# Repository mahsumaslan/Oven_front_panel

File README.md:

# Oven_front_panel
It is a front panel pcb and test program.

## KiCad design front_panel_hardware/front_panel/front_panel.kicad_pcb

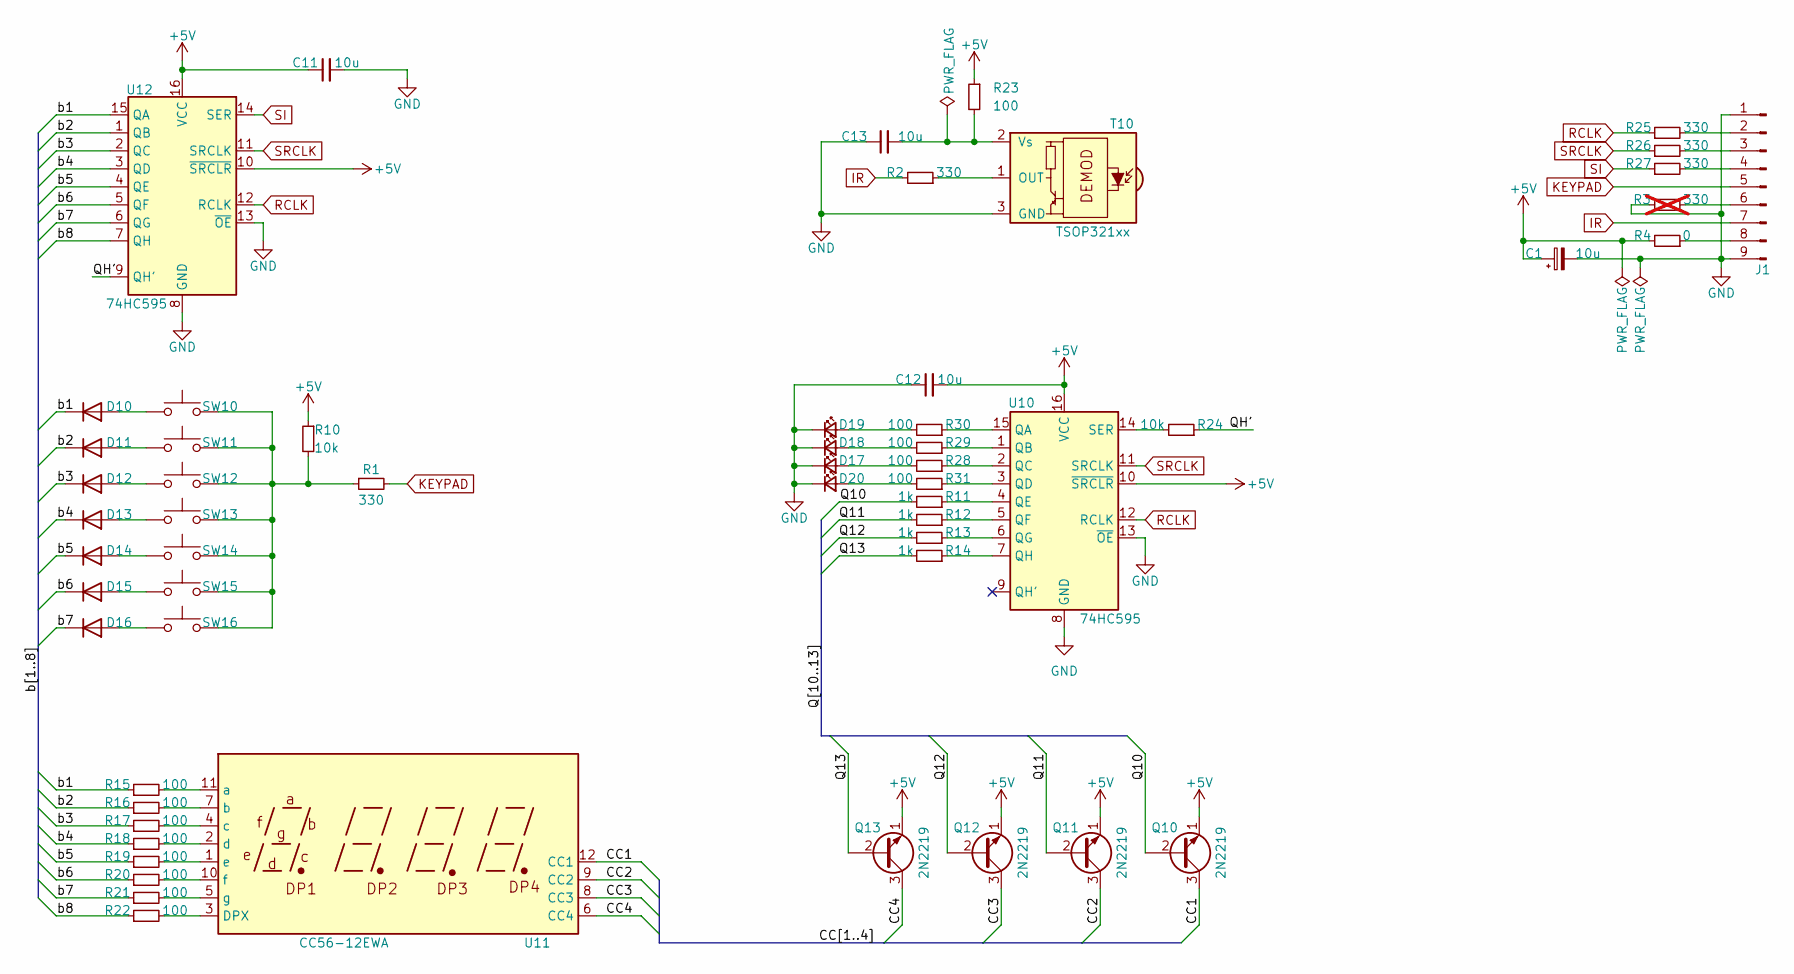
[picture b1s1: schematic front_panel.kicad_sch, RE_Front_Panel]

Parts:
C1, C11, C12, C13: 10u; C_Axial_L3.8mm_D2.6mm_P10.00mm_Horizontal
D10, D11, D12, D13, D14, D15, D16: 1N914; D_DO-35_SOD27_P7.62mm_Horizontal
D17, D18, D19, D20: LED_Small; LED_D3.0mm
J1: Conn_01x09_Pin; JST_EH_B9B-EH-A_1x09_P2.50mm_Vertical
Q10, Q11, Q12, Q13: 2N2219; TO-92_HandSolder
R1, R2, R25, R26, R27: 330; R_Axial_DIN0204_L3.6mm_D1.6mm_P5.08mm_Horizontal
R3: 330; R_Axial_DIN0204_L3.6mm_D1.6mm_P5.08mm_Horizontal; not fitted
R4: 0; R_Axial_DIN0204_L3.6mm_D1.6mm_P5.08mm_Horizontal
R10, R24: 10k; R_Axial_DIN0204_L3.6mm_D1.6mm_P5.08mm_Horizontal
R11, R12, R13, R14: 1k; R_Axial_DIN0204_L3.6mm_D1.6mm_P5.08mm_Horizontal
R15, R16, R17, R18, R19, R20, R21, R22, R23, R28, R29, R30, R31: 100; R_Axial_DIN0204_L3.6mm_D1.6mm_P5.08mm_Horizontal
SW10, SW11, SW12, SW13, SW14, SW15, SW16: SW_Push; SW_PUSH_6mm
T10: TSOP321xx; Vishay_MOLD-3Pin
U10, U12: 74HC595; DIP-16_W7.62mm_LongPads
U11: CC56-12EWA; CA56-12EWA

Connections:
+5V: C1.1, C11.1, C12.2, Q10.1 (E), Q11.1 (E), Q12.1 (E), Q13.1 (E), R4.2, R10.1, R23.1, U10.10 (~SRCLR), U10.16 (VCC), U12.10 (~SRCLR), U12.16 (VCC)
/CC1: Q10.3 (C), U11.12 (CC1)
/CC2: Q11.3 (C), U11.9 (CC2)
/CC3: Q12.3 (C), U11.8 (CC3)
/CC4: Q13.3 (C), U11.6 (CC4)
/Q10: Q10.2 (B), R11.2
/Q11: Q11.2 (B), R12.2
/Q12: Q12.2 (B), R13.2
/Q13: Q13.2 (B), R14.2
/QH': R24.1, U12.9 (QH')
/b1: D10.1 (K), R15.1, U12.15 (QA)
/b2: D11.1 (K), R16.1, U12.1 (QB)
/b3: D12.1 (K), R17.1, U12.2 (QC)
/b4: D13.1 (K), R18.1, U12.3 (QD)
/b5: D14.1 (K), R19.1, U12.4 (QE)
/b6: D15.1 (K), R20.1, U12.5 (QF)
/b7: D16.1 (K), R21.1, U12.6 (QG)
/b8: R22.1, U12.7 (QH)
GND: C1.2, C11.2, C12.1, C13.1, D17.1 (K), D18.1 (K), D19.1 (K), D20.1 (K), J1.1, J1.9, R3.1, T10.3 (GND), U10.8 (GND), U10.13 (~OE), U12.8 (GND), U12.13 (~OE)
IR: J1.7, R2.2
KEYPAD: J1.5, R1.2
unnamed: D10.2 (A), SW10.2
unnamed: D11.2 (A), SW11.2
unnamed: D12.2 (A), SW12.2
unnamed: D13.2 (A), SW13.2
unnamed: D14.2 (A), SW14.2
unnamed: D15.2 (A), SW15.2
unnamed: D16.2 (A), SW16.2
unnamed: D17.2 (A), R28.2
unnamed: D18.2 (A), R29.2
unnamed: D19.2 (A), R30.2
unnamed: D20.2 (A), R31.2
unnamed: J1.2, R25.2
unnamed: J1.3, R26.2
unnamed: J1.4, R27.2
unnamed: J1.6, R3.2
unnamed: J1.8, R4.1
unnamed: R1.1, R10.2, SW10.1, SW11.1, SW12.1, SW13.1, SW14.1, SW15.1, SW16.1
unnamed: R2.1, T10.1 (OUT)
unnamed: C13.2, R23.2, T10.2 (Vs)
unnamed: R30.1, U10.15 (QA)
unnamed: R29.1, U10.1 (QB)
unnamed: R28.1, U10.2 (QC)
unnamed: R31.1, U10.3 (QD)
unnamed: R11.1, U10.4 (QE)
unnamed: R12.1, U10.5 (QF)
unnamed: R13.1, U10.6 (QG)
unnamed: R14.1, U10.7 (QH)
unnamed: R24.2, U10.14 (SER)
unnamed: R22.2, U11.3 (DPX)
unnamed: R15.2, U11.11 (a)
unnamed: R16.2, U11.7 (b)
unnamed: R17.2, U11.4 (c)
unnamed: R18.2, U11.2 (d)
unnamed: R19.2, U11.1 (e)
unnamed: R20.2, U11.10 (f)
unnamed: R21.2, U11.5 (g)
RCLK: R25.1, U10.12 (RCLK), U12.12 (RCLK)
SI: R27.1, U12.14 (SER)
SRCLK: R26.1, U10.11 (SRCLK), U12.11 (SRCLK)

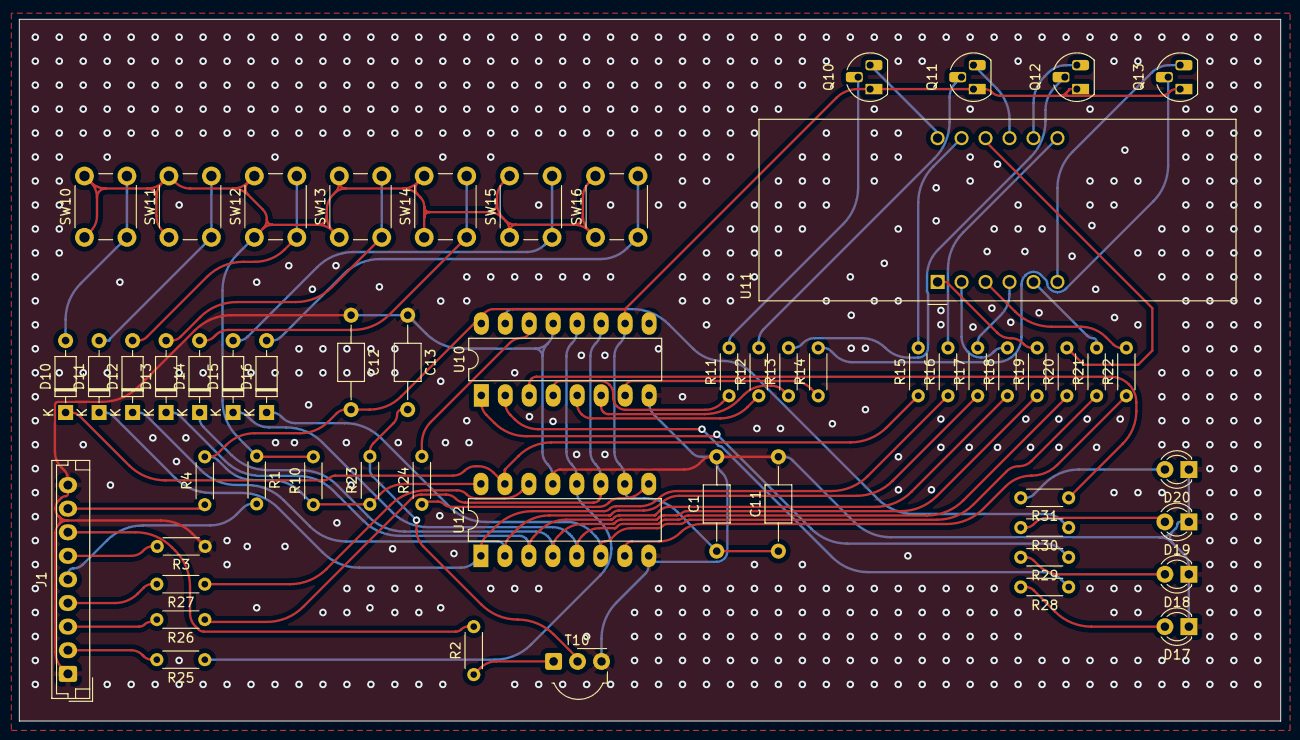
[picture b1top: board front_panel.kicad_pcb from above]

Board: 2 copper layers, 133.6 x 74.3 mm, 57 parts (0 on the bottom side), 60 nets.

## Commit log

2024-09-07 Update LICENSE
2024-09-07 Initial_commit.
    Upload old project file.
